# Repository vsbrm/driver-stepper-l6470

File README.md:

# Stepper motor driver board

This is the simple stepper motor driver board which built on L6470 IC.
This IC can rule one bipolar stepper motor in up to 1/128 microstepping mode
with current control, overcurrent protection and set up by SPI interface.
This board can be used as completed part of stepper motor control system.

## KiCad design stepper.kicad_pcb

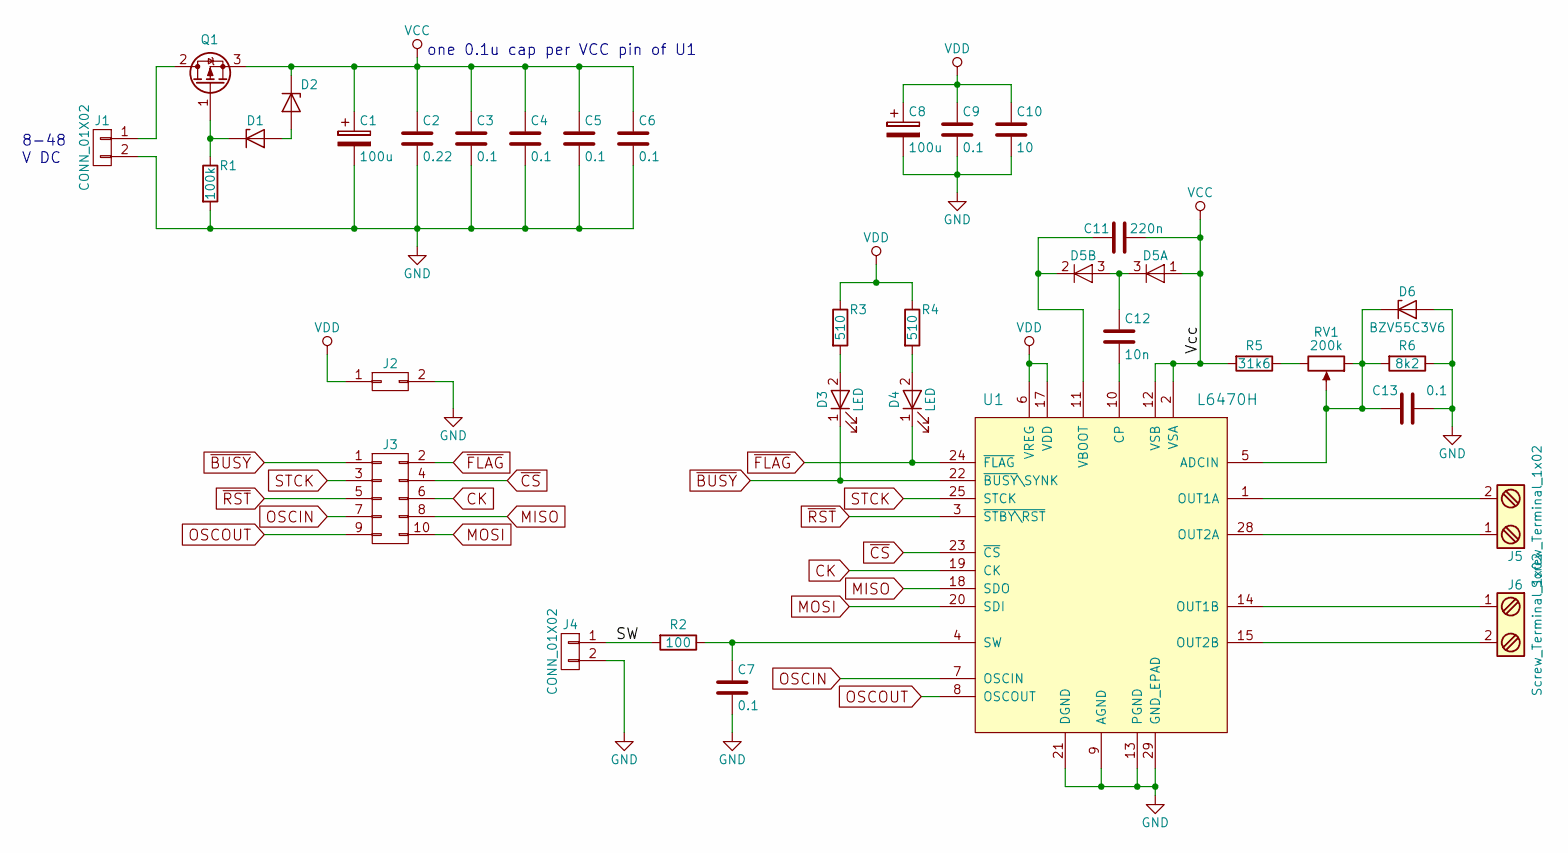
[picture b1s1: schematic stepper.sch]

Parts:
C1, C8: 100u; CP_Radial_D10.0mm_P3.50mm; Voltage 100
C2: 0.22; C_0805; Voltage 100
C3, C4, C5, C6, C9: 0.1; C_0805; Voltage 25
C7, C13: 0.1; C_0805; Voltage 6.3
C10: 10; C_0805; Voltage 25
C11: 220n; C_0805; Voltage 16v
C12: 10n; C_0805; Voltage 50v
D1, D2: BZV55C10; D_MiniMELF
D3, D4: LED; LED_0805
D5: BAV99; SOT-23
D6: BZV55C3V6; D_MiniMELF
J1, J4: CONN_01X02; Pin_Header_Straight_1x02_Pitch2.54mm
J2: CONN_02X01; Pin_Header_Straight_1x02_Pitch2.54mm
J3: CONN_02X05; Pin_Header_Straight_2x05_Pitch2.54mm
J5, J6: Screw_Terminal_1x02; TerminalBlock_bornier-2_P5.08mm
Q1: IRFR5410; TO-252-2
R1: 100k; R_0805
R2: 100; R_0805
R3, R4: 510; R_0805
R5: 31k6; R_0805
R6: 8k2; R_0805
RV1: 200k; Potentiometer_Trimmer_Bourns_3266W
U1: L6470H; HTSSOP-28_4.4x9.7mm_Pitch0.65mm_ThermalPad

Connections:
/SW: J4.1, R2.2
CK: J3.6, U1.19 (CK)
GND: C1.2, C2.2, C3.2, C4.2, C5.2, C6.2, C7.2, C8.2, C9.2, C10.2, C13.1, D6.2 (A), J1.2, J2.2, J4.2, R1.2, R6.1, U1.9 (AGND), U1.13 (PGND), U1.21 (DGND), U1.27 (PGND), U1.29 (GND_EPAD)
MISO: J3.8, U1.18 (SDO)
MOSI: J3.10, U1.20 (SDI)
unnamed: C7.1, R2.1, U1.4 (SW)
unnamed: C11.1, D5.2 (K), U1.11 (VBOOT)
unnamed: C12.1, D5.3 (K)
unnamed: C12.2, U1.10 (CP)
unnamed: C13.2, D6.1 (K), R6.2, RV1.1, RV1.2, U1.5 (ADCIN)
unnamed: D1.1 (K), Q1.1 (G), R1.1
unnamed: D1.2 (A), D2.2 (A)
unnamed: D3.2 (A), R3.2
unnamed: D4.2 (A), R4.2
unnamed: J1.1, Q1.2 (D)
unnamed: J5.1, U1.28 (OUT2A)
unnamed: J5.2, U1.1 (OUT1A)
unnamed: J6.1, U1.14 (OUT1B)
unnamed: J6.2, U1.15 (OUT2B)
unnamed: R5.1, RV1.3
OSCIN: J3.7, U1.7 (OSCIN)
OSCOUT: J3.9, U1.8 (OSCOUT)
STCK: J3.3, U1.25 (STCK)
VCC: C1.1, C2.1, C3.1, C4.1, C5.1, C6.1, C11.2, D2.1 (K), D5.1 (A), Q1.3 (S), R5.2, U1.2 (VSA), U1.12 (VSB), U1.16 (VSB), U1.26 (VSA)
VDD: C8.1, C9.1, C10.1, J2.1, R3.1, R4.1, U1.6 (VREG), U1.17 (VDD)
~BUSY: D3.1 (K), J3.1, U1.22 (~BUSY~\SYNK)
~CS: J3.4, U1.23 (~CS)
~FLAG: D4.1 (K), J3.2, U1.24 (~FLAG)
~RST: J3.5, U1.3 (~STBY\RST)

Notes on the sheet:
8-48 V DC
one 0.1u cap per VCC pin of U1

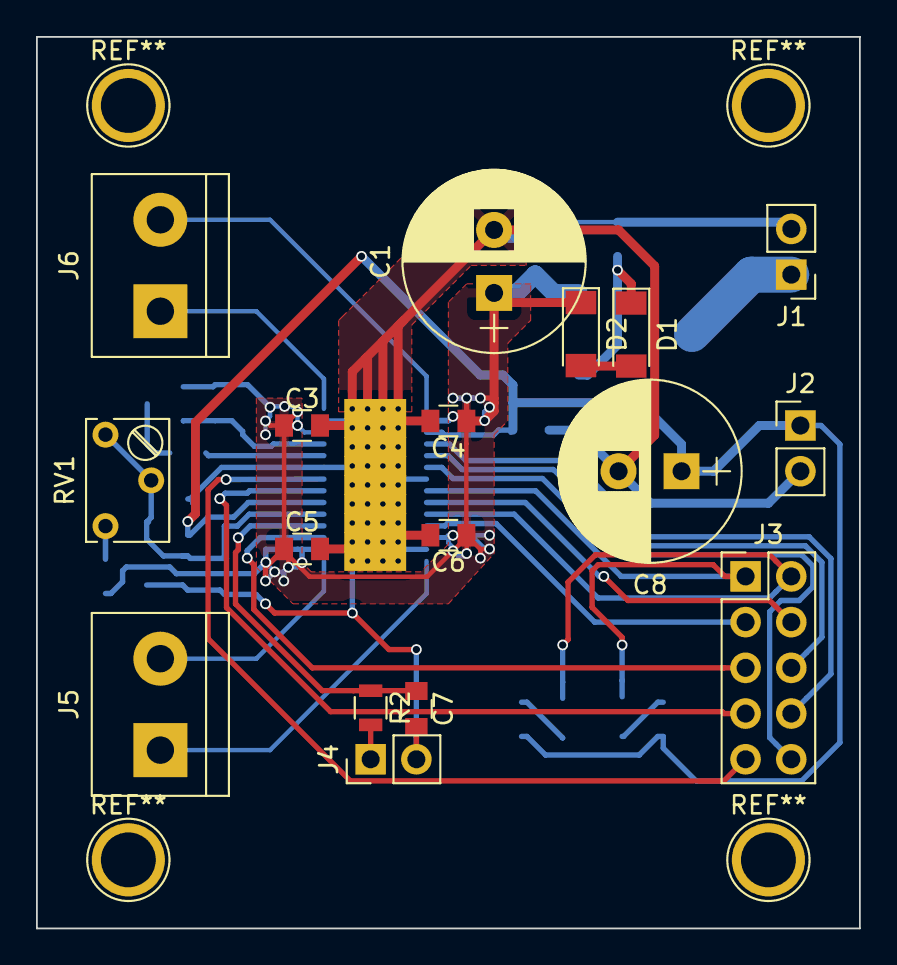
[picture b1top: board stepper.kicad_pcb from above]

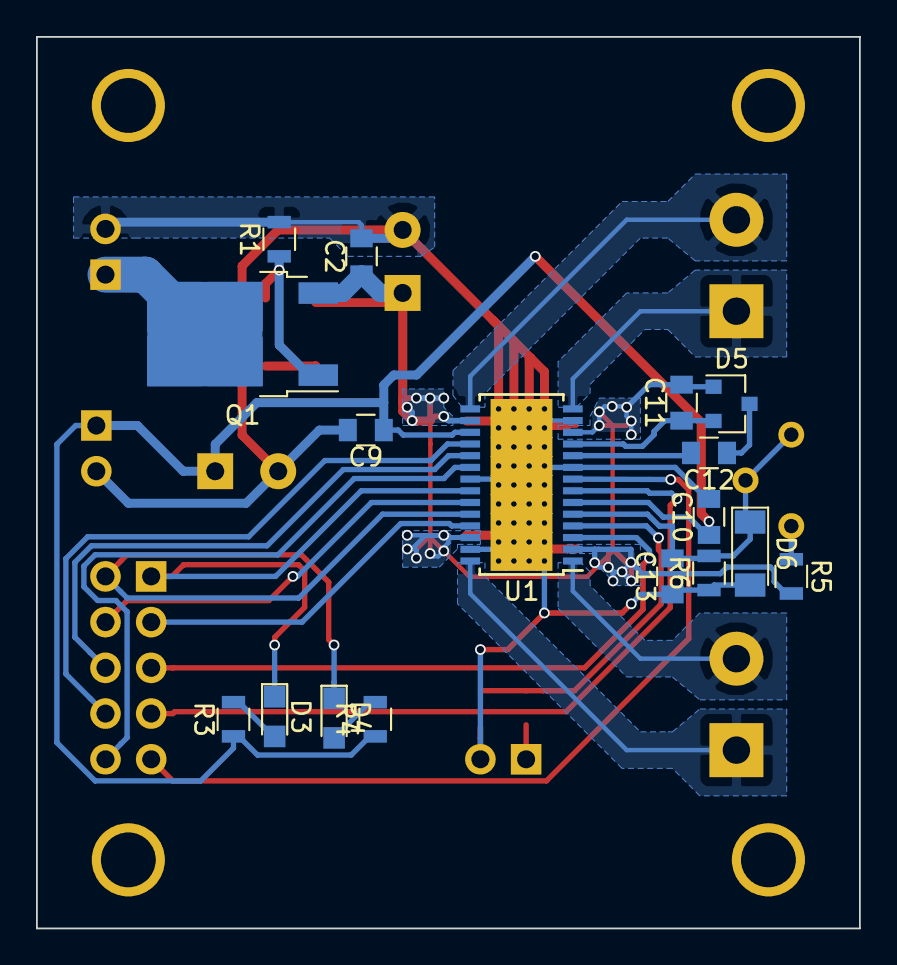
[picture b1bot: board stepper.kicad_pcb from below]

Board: 2 copper layers, 45.7 x 49.5 mm, 34 parts (17 on the bottom side), 29 nets.

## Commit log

2018-02-07 initial
2018-03-11 Values
    Viable version of schematic. Calculated values and attached footprints.
2018-03-11 Caps
    Some changes in VCC filtration capcitors.
2018-03-17 PCB
    Routed PCB
